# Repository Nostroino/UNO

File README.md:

")

Esquemático do NostroINO. [[PDF](https://github.com/nostroino/UNO/blob/master/SCH%20Nostroino%20UNO.pdf)]

No diretório [KiCad](https://github.com/nostroino/UNO/tree/master/KiCad) encontram-se todos os *Source Files* da placa disponíveis para edição. Recomenda-se utilizar a [versão 4.0.2 do KiCad](http://kicad-pcb.org/download/) ou posterior. Para faciitar dê um *Fork* em todo o diretório.

Encorajamos o uso do material disponível! Só não esqueça de atribuir crédito, como preconiza a [CC BY-SA 3.0 BR](http://creativecommons.org/licenses/by-sa/3.0/br).

Qualquer dúvida, sugestão... pode entrar em contato conosco.

Um abraço!

[_André Augusto Andreis_](<andreis.andre@gmail.com> ) e [_Diego Volpini_](<diego.volpini@gmail.com>)

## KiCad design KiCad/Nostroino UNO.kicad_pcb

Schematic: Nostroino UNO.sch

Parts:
C1, C6, C8, C9: 100nF
C3, C4: 22pF
C5: 10uF
C7: 10nF
CH1: RESET
D1: 1N4007
D2: LIGADO
D3: TX
D4: RX
D5: L
J1: USB/EXT
R1, R2, R4, R5, R6, R7, R8: 1K
R3: 10K
U1: 7805
U2: ATMEGA368P-PU
U3: FT232RL
X1: Alimentação
X2: USB
X3: POWER
X4, X7: DIGITAL (PWM#)
X5: ICSP
X6: ANALOG IN
X8: Fix1
X9: Fix2
X10: Fix3
X11: Fix4
XTAL1: 16MHz

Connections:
+3.3V: C8.1, U3.17 (3V3OUT), X3.5
+5V: D3.A (Anôdo), D4.A (Anôdo), J1.2, R1.2, R3.2, U2.7 (VCC), U2.20 (AVCC), U3.4 (VCCIO), U3.20 (VCC), X3.4, X3.7, X5.2
/AREF: C1.1, U2.21 (AREF), X4.8
/MISO: U2.18 (PB4(PCINT4/MISO)), X4.5, X5.1
/MOSI: U2.17 (PB3(PCINT3/OC2A/MOSI)), X4.4, X5.4
/RESET: C9.2, CH1.2, R3.1, U2.1 ((PCINT14/~RESET~)PC6), X3.6, X5.5
/RX: R4.2, U2.2 ((PCINT16/RXD)PD0), X7.1
/SCK: R8.2, U2.19 (PB5(PCINT5/SCK)), X4.6, X5.3
/SCL: U2.28 ((PCINT14/SCL/ADC5)PC5), X4.10, X6.1
/SDA: U2.27 ((PCINT12/SDA/ADC4)PC4), X4.9, X6.2
/TX: R5.2, U2.3 ((PCINT17/TXD)PD1), X7.2
DTR: C9.1, R2.2, U3.2 (DTR#)
GND: C1.2, C3.2, C4.2, C5.-, C6.2, C7.2, C8.2, CH1.1, D2.K (Catôdo), D5.K (Catôdo), R2.1, U1.2 (Ground), U2.8 (GND), U2.22 (GND), U3.7 (GND), U3.18 (GND), U3.21 (GND), U3.25 (AGND), U3.26 (TEST), X1.2, X2.4 (GND), X3.2, X3.3, X4.7, X5.6
unnamed: D1.A, X1.1
unnamed: C7.1, J1.3, X2.1 (VCC)
unnamed: R4.1, U3.1 (TX)
unnamed: D2.A (Anôdo), R1.1
unnamed: R5.1, U3.5 (RX)
unnamed: U2.24 ((PCINT9/ADC1)PC1), X6.5
unnamed: U2.12 ((PCINT22/OC0A/AIN0)PD6), X7.7
unnamed: U2.11 ((PCINT21/OC0B/T1)PD5), X7.6
unnamed: U2.6 ((PCINT20/XCK/T0)PD4), X7.5
unnamed: U2.5 ((PCINT19/OC2B/INT1)PD3), X7.4
unnamed: U2.4 ((PCINT18/INT0)PD2), X7.3
unnamed: U2.26 ((PCINT11/ADC3)PC3), X6.3
unnamed: U2.25 ((PCINT10/ADC2)PC2), X6.4
unnamed: U2.13 ((PCINT23/AIN1)PD7), X7.8
unnamed: U2.23 ((PCINT8/ADC0)PC0), X6.6
unnamed: U2.14 (PB0(PCINT0/CLKO/ICP1)), X4.1
unnamed: U2.16 (PB2(PCINT2/OC1B/~SS~)), X4.3
unnamed: U2.15 (PB1(PCINT1/OC1A)), X4.2
unnamed: D5.A (Anôdo), R8.1
unnamed: R7.1, U3.22 (CBUS1)
unnamed: R6.1, U3.23 (CBUS0)
unnamed: D4.K (Catôdo), R7.2
unnamed: D3.K (Catôdo), R6.2
unnamed: C4.1, U2.10 (PB7(PCINT7/XTAL2/TOSC2)), XTAL1.2
unnamed: C3.1, U2.9 (PB6(PCINT6/XTAL1/TOSC1)), XTAL1.1
unnamed: C5.+, C6.1, J1.1, U1.3 (Output)
USB D+: U3.15 (USBDP), X2.3 (D+)
USB D-: U3.16 (USBDM), X2.2 (D-)
Vin: D1.K, U1.1 (Input), X3.1

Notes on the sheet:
7-12Vcc
10#
11#
GND
AREF
Vin
3,3V
RESET
IOREF
RX<0
TX>1

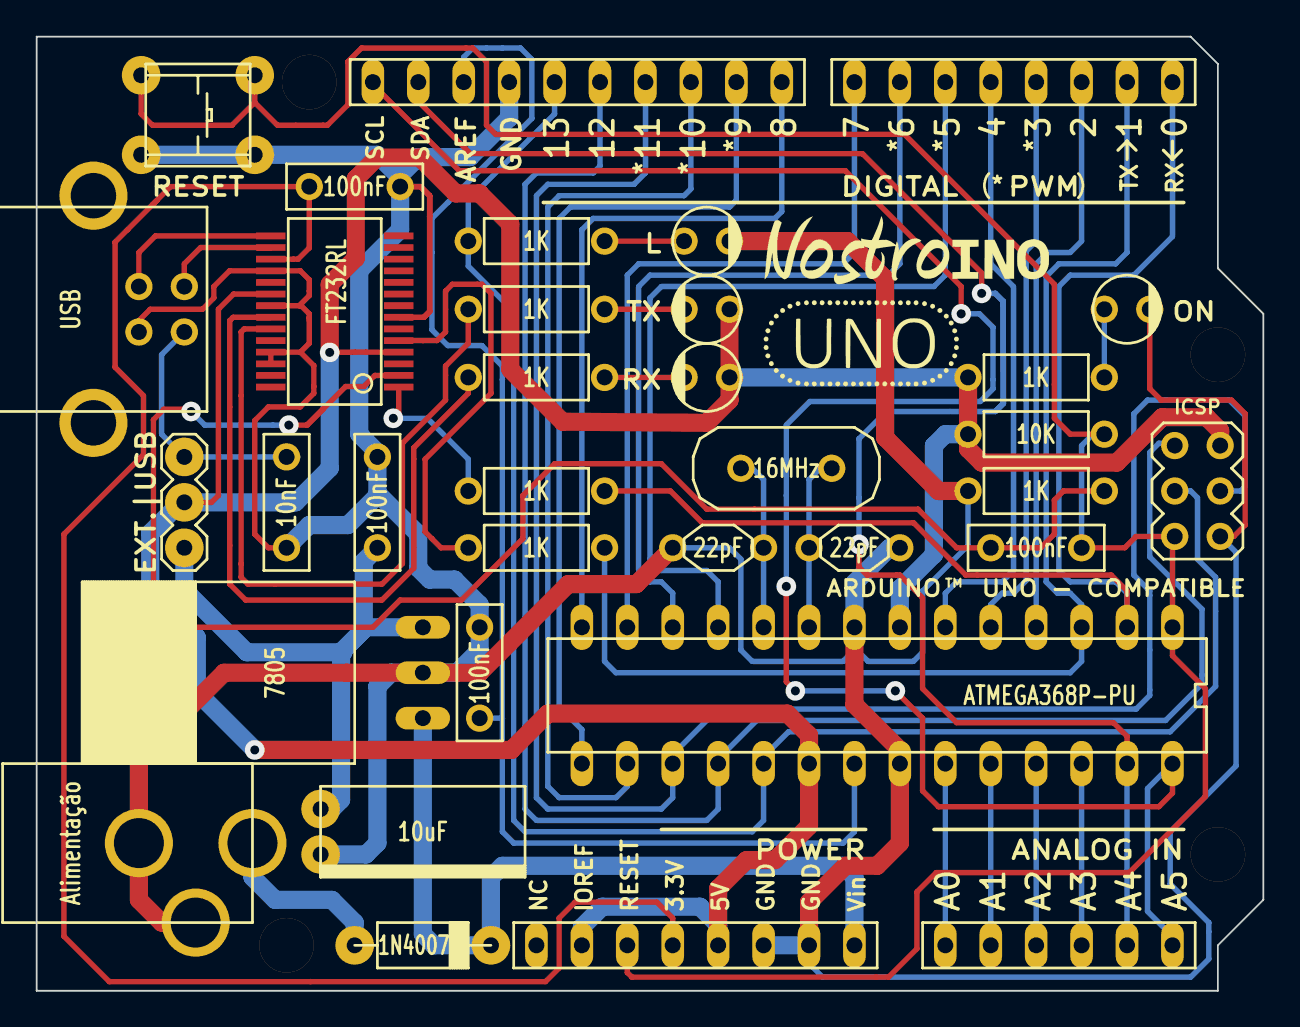
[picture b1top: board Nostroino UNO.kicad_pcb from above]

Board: 2 copper layers, 68.6 x 53.3 mm, 45 parts (0 on the bottom side), 42 nets.

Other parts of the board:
VAL: REF; OSHW-logo_B.SilkS_8mm_flipped
VAL#2: REF; CC-logo_B.SilkS_5mm_flipped
VAL#3: REF; BY-logo_B.SilkS_5mm_flipped
VAL#4: REF; SA-logo_B.SilkS_5mm_flipped
VAL#5: REF; UNO-logo_F.SilkS_11mm
VAL#6: REF; Nostroino-logo_F.SilkS_16mm
VAL#7: REF; Nostroino_UNO-logo_B.SilkS_34.29mm_flipped

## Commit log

2015-01-27 KiCad Files
2015-01-27 Rename Folders
2015-01-27 Readme Update
2015-02-04 Update Silk PCB
2015-02-04 Silks Updates
2015-02-04 Schematic Nostroino UNO [pdf]
2015-02-05 KiCad PCB Updat
    - GND USB passando para trilha 1A;
    - N-000004 passando para trilha 1A;
    - Sinal “+” no footprint no Cap. 10uF;
    - Aumentar furos do “EXT./USB” e ICSP;
    - Atualização Board Version para 2015.02.05.
2015-02-05 deleted
2015-02-05 KiCad
2015-02-05 KiCad
    Adição de Zonas F. Cu e B. Cu
2016-03-11 Little Changes
2016-03-11 3D Shapes
2016-03-12 Readme
2016-03-12 e-mail
